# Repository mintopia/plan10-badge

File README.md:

# P-LAN #10 Badge Challenge

## Introduction

This is a challenge coin/electronic badge for P-LAN #10 LAN party. It's a custom PCB designed in KiCad and firmware for an ATTiny402. It runs on 2 x AAA batteries with a voltage booster to provide the ~ 5V needed for the WS2812B LEDs.

The original design was missing reverse polarity protection. I've thrown a diode in on the ground connection to prevent this but I need to look into this more.

The badge has hints to the solution printed on it and if you read the code, you can see how it works.

## Thanks

Thanks to people in the DEFCON 32 Badge Hacking discord for inspiration and everyone in the #BadgeLife community.

## License

The MIT License (MIT)

Copyright (c) 2024 Jessica Smith

Permission is hereby granted, free of charge, to any person obtaining a copy
of this software and associated documentation files (the "Software"), to deal
in the Software without restriction, including without limitation the rights
to use, copy, modify, merge, publish, distribute, sublicense, and/or sell
copies of the Software, and to permit persons to whom the Software is
furnished to do so, subject to the following conditions:

The above copyright notice and this permission notice shall be included in
all copies or substantial portions of the Software.

THE SOFTWARE IS PROVIDED "AS IS", WITHOUT WARRANTY OF ANY KIND, EXPRESS OR
IMPLIED, INCLUDING BUT NOT LIMITED TO THE WARRANTIES OF MERCHANTABILITY,
FITNESS FOR A PARTICULAR PURPOSE AND NONINFRINGEMENT. IN NO EVENT SHALL THE
AUTHORS OR COPYRIGHT HOLDERS BE LIABLE FOR ANY CLAIM, DAMAGES OR OTHER
LIABILITY, WHETHER IN AN ACTION OF CONTRACT, TORT OR OTHERWISE, ARISING FROM,
OUT OF OR IN CONNECTION WITH THE SOFTWARE OR THE USE OR OTHER DEALINGS IN
THE SOFTWARE.

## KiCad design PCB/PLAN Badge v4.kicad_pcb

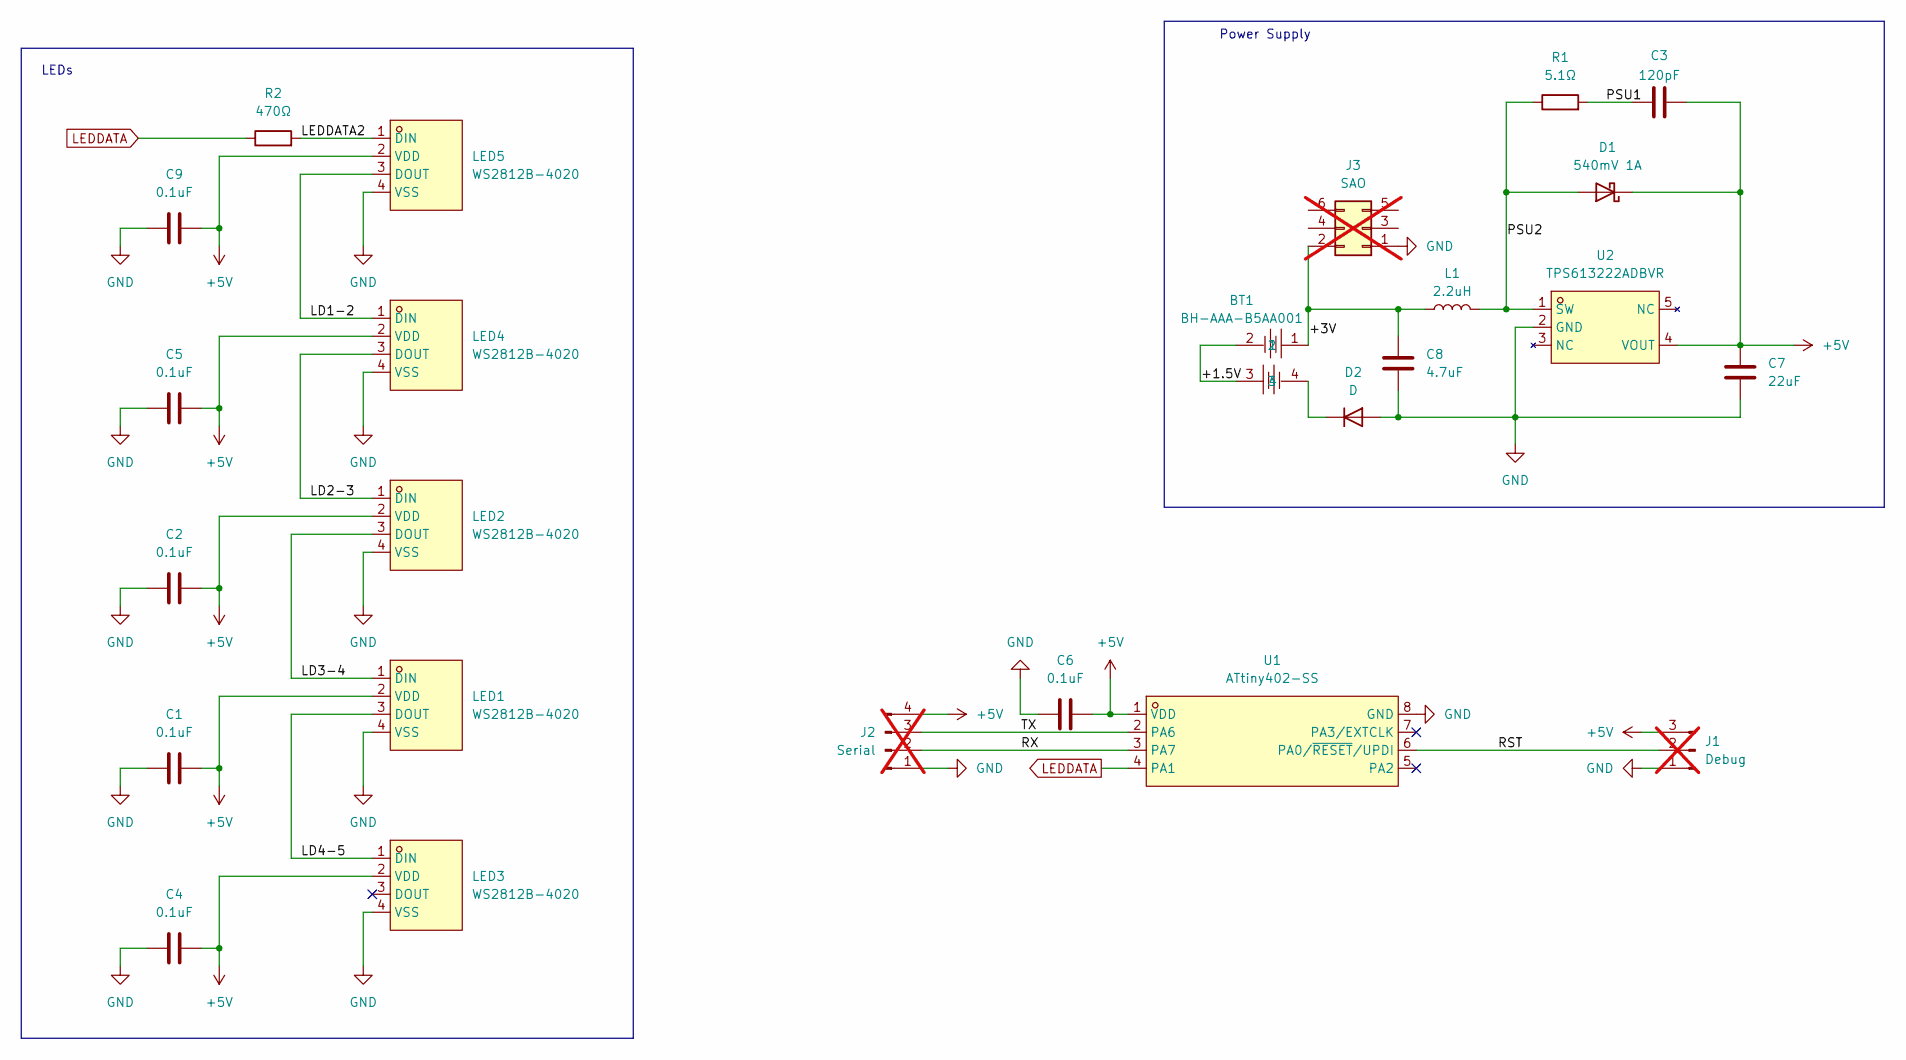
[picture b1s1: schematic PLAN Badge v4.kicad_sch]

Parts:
BT1: BH-AAA-B5AA001; BAT-SMD_BH-AAA-B5AA001; LCSC Part C964881
C1, C2, C4, C5, C6, C9: 0.1uF; C_0805_2012Metric_Pad1.18x1.45mm_HandSolder
C3: 120pF; C_0805_2012Metric_Pad1.18x1.45mm_HandSolder
C7: 22uF; C_0805_2012Metric_Pad1.18x1.45mm_HandSolder
C8: 4.7uF; C_0805_2012Metric_Pad1.18x1.45mm_HandSolder
D1: 540mV 1A; D_SOD-323_HandSoldering
D2: D; D_0805_2012Metric_Pad1.15x1.40mm_HandSolder
J1: Debug; PinHeader_1x03_P2.54mm_Vertical; not fitted
J2: Serial; PinHeader_1x04_P2.54mm_Vertical; not fitted
J3: SAO; PinHeader_2x03_P2.54mm_Vertical; not fitted
L1: 2.2uH; L0806
LED1, LED2, LED3, LED4, LED5: WS2812B-4020; LED-SMD_WS2812B-4020; LCSC Part C965557
R1: 5.1Ω; R_0805_2012Metric_Pad1.20x1.40mm_HandSolder
R2: 470Ω; R_0805_2012Metric_Pad1.20x1.40mm_HandSolder
U1: ATtiny402-SS; SOIC-8_L4.9-W3.9-P1.27-LS6.0-BL; LCSC Part C616056
U2: TPS613222ADBVR; TSOT-23-5_L2.9-W1.6-P0.95-LS2.8-BR; LCSC Part C2071163

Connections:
+5V: C1.2, C2.2, C3.2, C4.2, C5.2, C6.2, C7.2, C9.2, D1.1 (K), J1.3, J2.4, LED1.2 (VDD), LED2.2 (VDD), LED3.2 (VDD), LED4.2 (VDD), LED5.2 (VDD), U1.1 (VDD), U2.4 (VOUT)
/+1.5V: BT1.2, BT1.3
/+3V: BT1.1, C8.1, J3.2, L1.1
/LD1-2: LED4.1 (DIN), LED5.3 (DOUT)
/LD2-3: LED2.1 (DIN), LED4.3 (DOUT)
/LD3-4: LED1.1 (DIN), LED2.3 (DOUT)
/LD4-5: LED1.3 (DOUT), LED3.1 (DIN)
/LEDDATA2: LED5.1 (DIN), R2.2
/PSU1: C3.1, R1.2
/PSU2: D1.2 (A), L1.2, R1.1, U2.1 (SW)
/RST: J1.2, U1.6 (PA0/~RESET/UPDI)
/RX: J2.2, U1.3 (PA7)
/TX: J2.3, U1.2 (PA6)
GND: C1.1, C2.1, C4.1, C5.1, C6.1, C7.1, C8.2, C9.1, D2.2 (A), J1.1, J2.1, J3.1, LED1.4 (VSS), LED2.4 (VSS), LED3.4 (VSS), LED4.4 (VSS), LED5.4 (VSS), U1.8 (GND), U2.2 (GND)
LEDDATA: R2.1, U1.4 (PA1)
unnamed: BT1.4, D2.1 (K)

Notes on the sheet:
Power Supply
LEDs

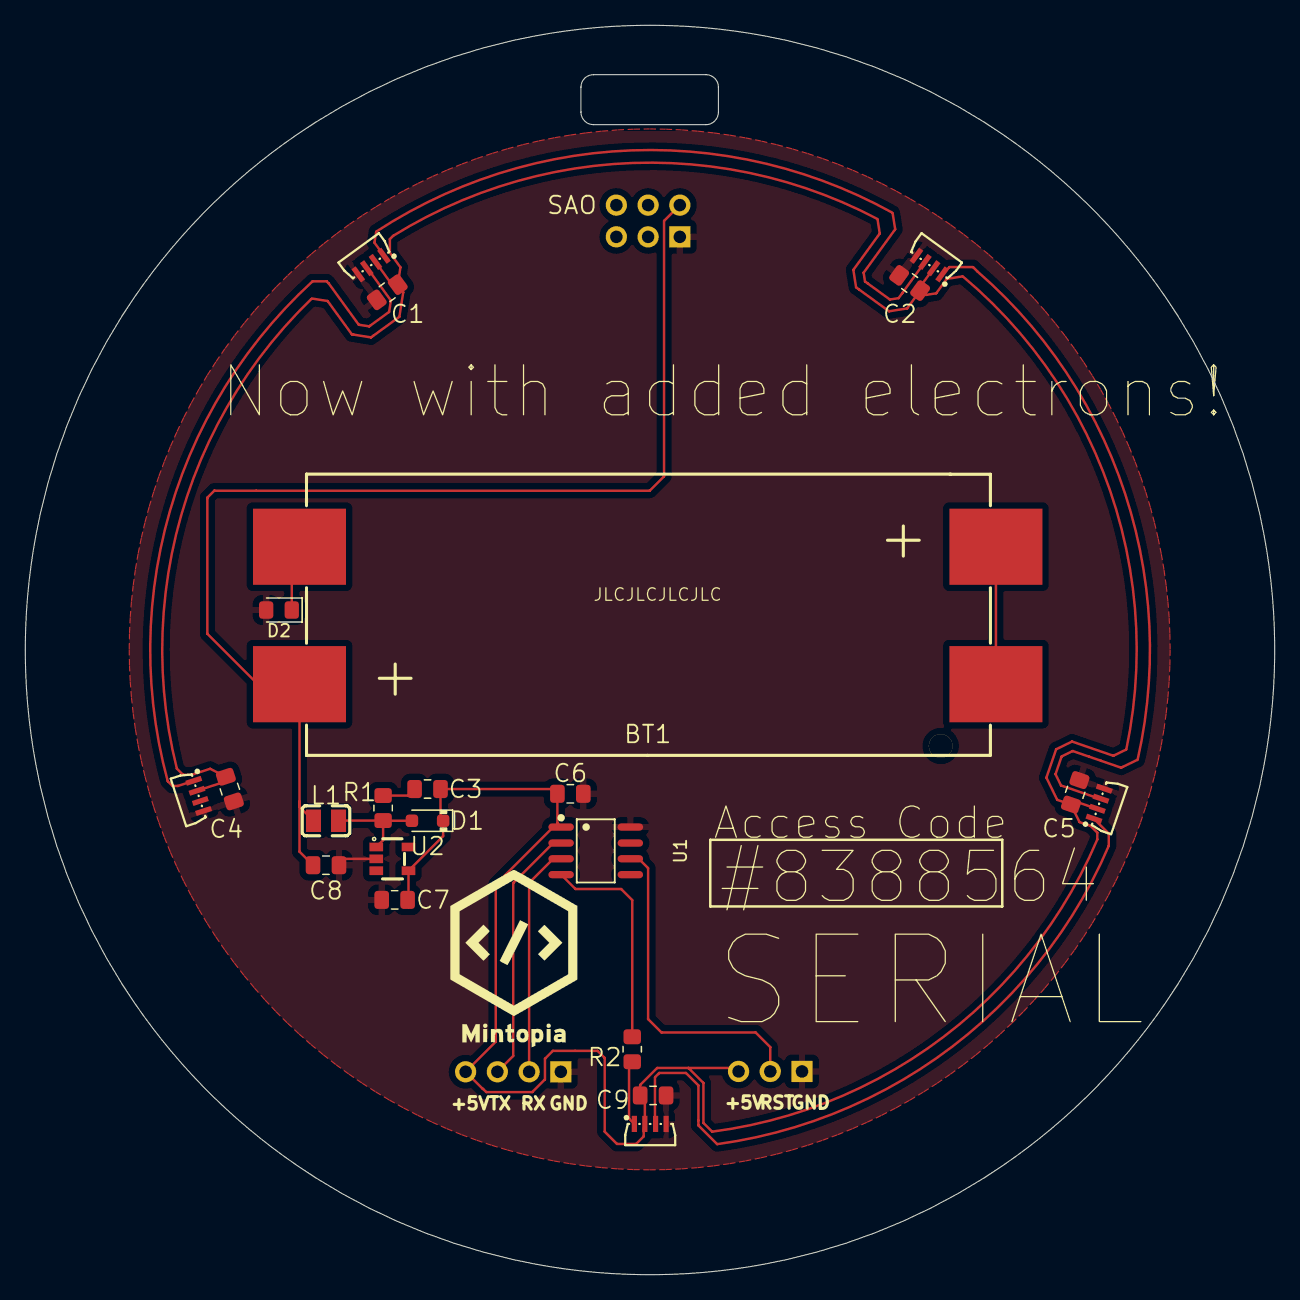
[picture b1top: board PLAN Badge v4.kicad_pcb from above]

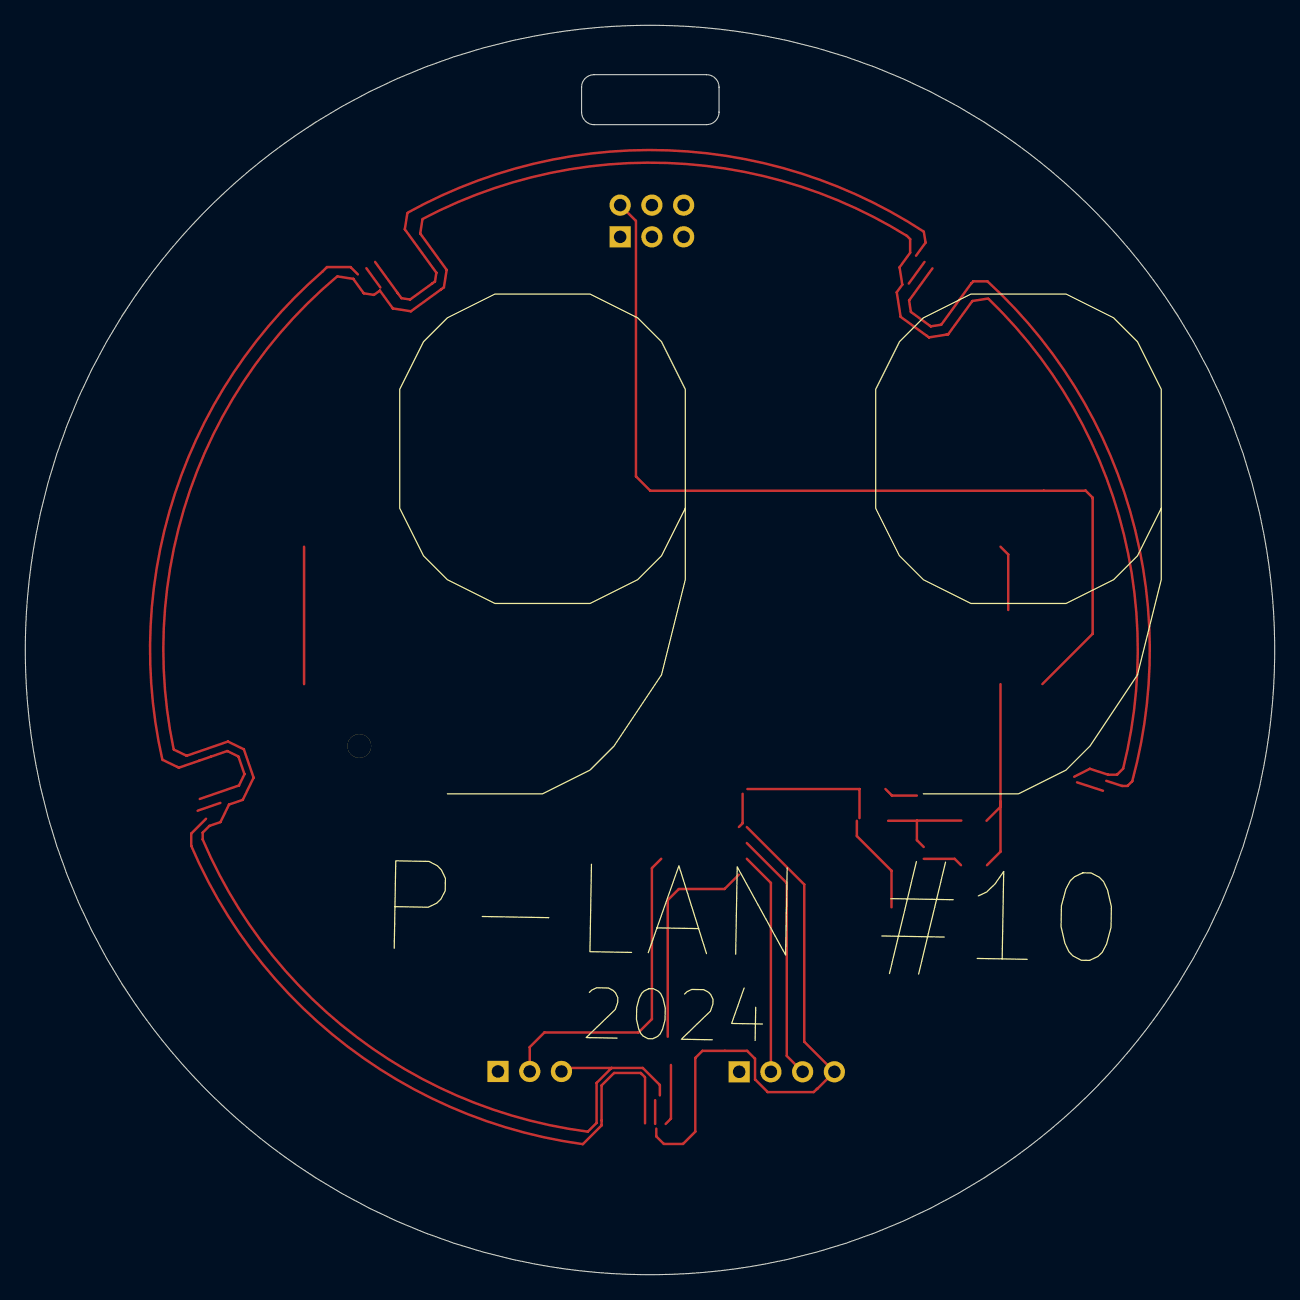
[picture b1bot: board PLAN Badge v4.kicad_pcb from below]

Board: 2 copper layers, 100.0 x 100.0 mm, 25 parts (2 on the bottom side), 16 nets.
